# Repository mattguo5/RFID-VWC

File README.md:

# RFID-VWC

The RFID-VWC Github repository serves to document all of the hardware and software implementations for the Oregon State University OPEnS RFID Moisture project.

Directory information:

BOM

    - Contains the most up-to-date BOM of the overall project
  
Code

  - Adafruit_Logging
  
        - Contains the most up-to-date Adafruit STEMMA Soil Moisture firmware code
      
  - Implementation
  
        - Contains the Feather M0 port of firmware for the RFID Sensor
  - src
  
        - Includes all dependencies needed to compile the above .ino files
      
Hardware

    -Contains .brd and .sch files of the RFID-Feather Interface Boards for communication with the Feather M0

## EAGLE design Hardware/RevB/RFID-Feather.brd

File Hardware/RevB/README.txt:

Here contains the board and schematic files for the RevB board Interface Board.

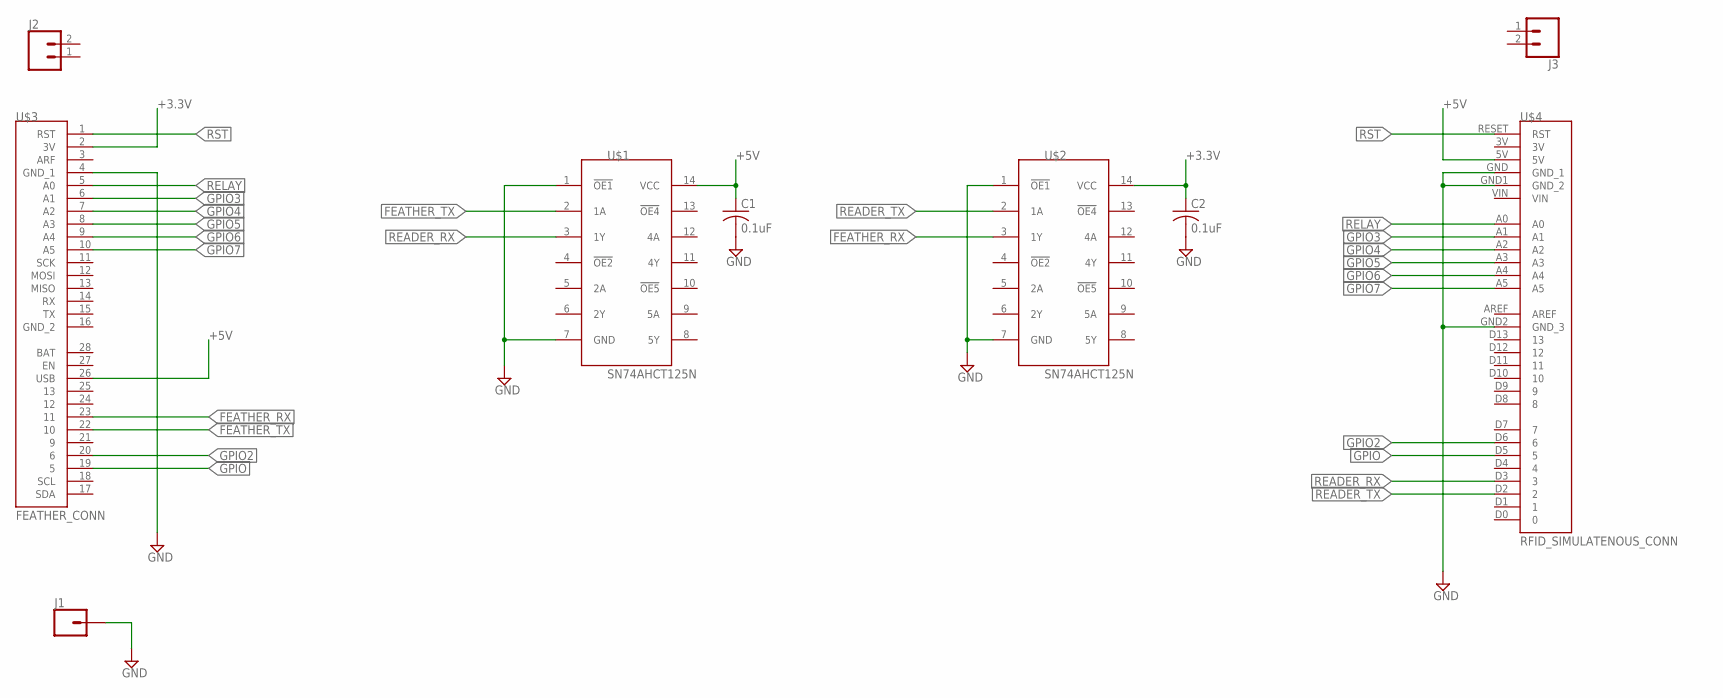
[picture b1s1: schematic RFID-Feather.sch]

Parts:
C1, C2: 0.1uF; C0805K
J1: CONN_01PTH_2MM; 1X01_2MM
J2, J3: CONN_02; 1X02
U$1, U$2: SN74AHCT125N; DIP254P762X508-14P
U$3: FEATHER_CONN; FEATHERWING
U$4: RFID_SIMULATENOUS_CONN; ARDUINO

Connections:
+3.3V: C2.1, U$2.14 (VCC), U$3.2 (3V)
+5V: C1.1, U$1.14 (VCC), U$3.26 (USB), U$4.5V
FEATHER_RX: U$2.3 (1Y), U$3.23 (11)
FEATHER_TX: U$1.2 (1A), U$3.22 (10)
GND: C1.2, C2.2, J1.1, U$1.1 (!OE1), U$1.7 (GND), U$2.1 (!OE1), U$2.7 (GND), U$3.4 (GND_1), U$4.GND (GND_1), U$4.GND1 (GND_2), U$4.GND2 (GND_3)
GPIO: U$3.19 (5), U$4.D5 (5)
GPIO2: U$3.20 (6), U$4.D6 (6)
GPIO3: U$3.6 (A1), U$4.A1
GPIO4: U$3.7 (A2), U$4.A2
GPIO5: U$3.8 (A3), U$4.A3
GPIO6: U$3.9 (A4), U$4.A4
GPIO7: U$3.10 (A5), U$4.A5
READER_RX: U$1.3 (1Y), U$4.D3 (3)
READER_TX: U$2.2 (1A), U$4.D2 (2)
RELAY: U$3.5 (A0), U$4.A0
RST: U$3.1 (RST), U$4.RESET (RST)

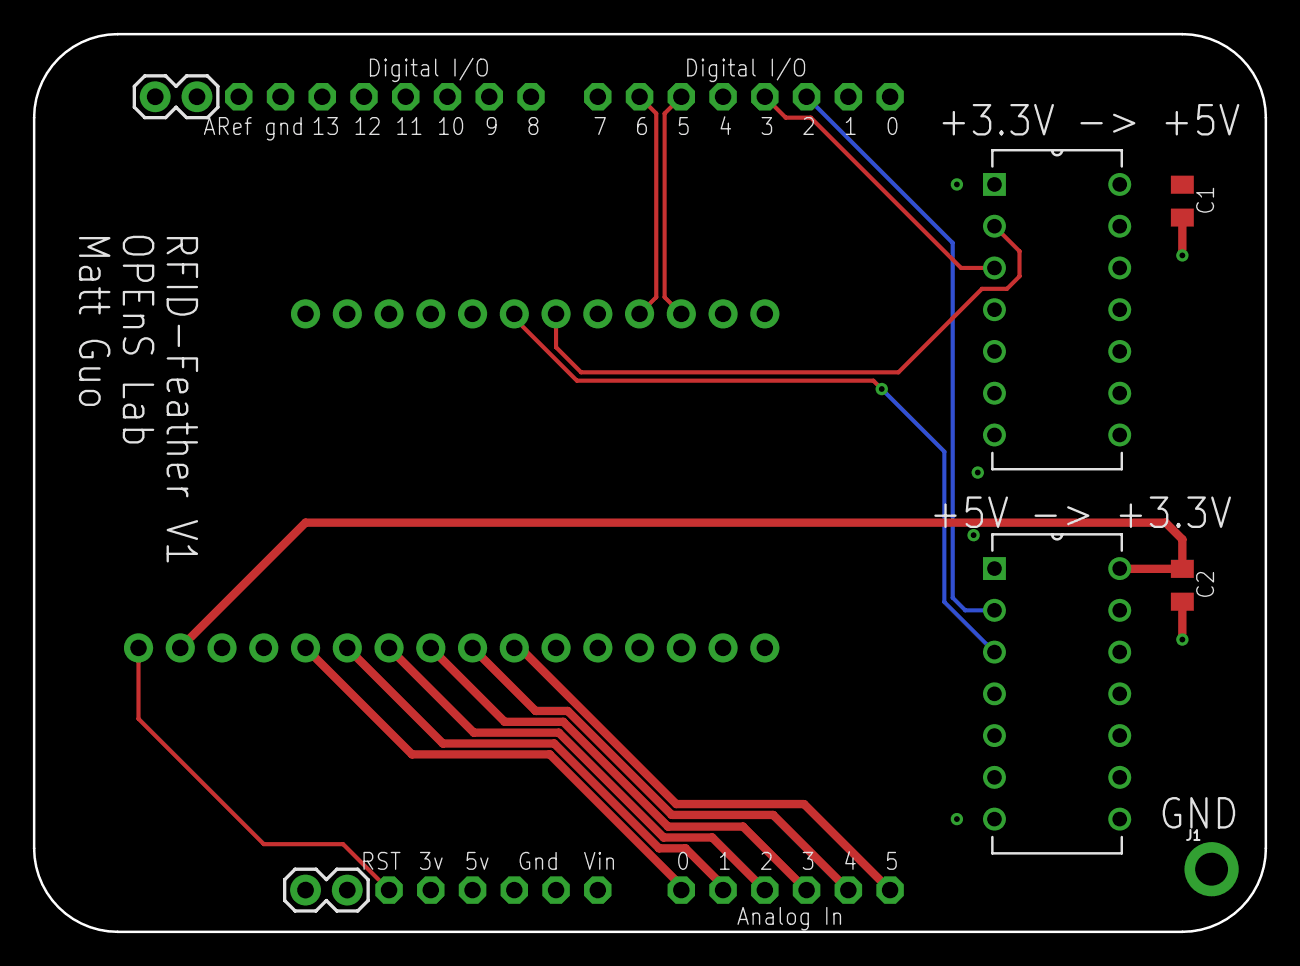
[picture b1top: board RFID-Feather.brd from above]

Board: 2 copper layers, 74.9 x 54.6 mm, 9 parts (0 on the bottom side), 16 nets.

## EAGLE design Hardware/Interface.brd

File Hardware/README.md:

This is the .sch and .brd of the interface board for the Sparkfun RFID reader and Feather M0

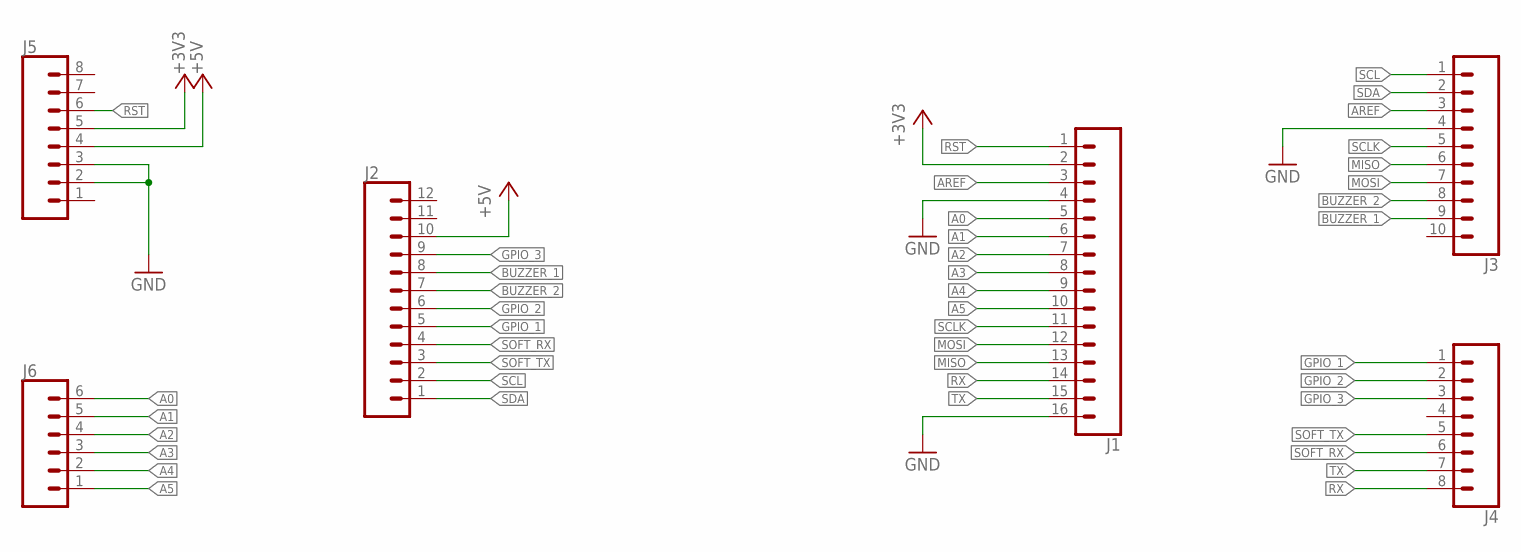
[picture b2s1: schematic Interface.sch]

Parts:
J1: CONN_16; 1X16
J2: CONN_12; 1X12
J3: CONN_10"; 1X10
J4, J5: CONN_08"; 1X08
J6: CONN_06SILK_FEMALE_PTH; 1X06

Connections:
+3V3: J1.2, J5.5
+5V: J2.10, J5.4
A0: J1.5, J6.6
A1: J1.6, J6.5
A2: J1.7, J6.4
A3: J1.8, J6.3
A4: J1.9, J6.2
A5: J1.10, J6.1
AREF: J1.3, J3.3
BUZZER_1: J2.8, J3.9
BUZZER_2: J2.7, J3.8
GND: J1.4, J1.16, J3.4, J5.2, J5.3
GPIO_1: J2.5, J4.1
GPIO_2: J2.6, J4.2
GPIO_3: J2.9, J4.3
MISO: J1.13, J3.6
MOSI: J1.12, J3.7
RST: J1.1, J5.6
RX: J1.14, J4.8
SCL: J2.2, J3.1
SCLK: J1.11, J3.5
SDA: J2.1, J3.2
SOFT_RX: J2.4, J4.6
SOFT_TX: J2.3, J4.5
TX: J1.15, J4.7

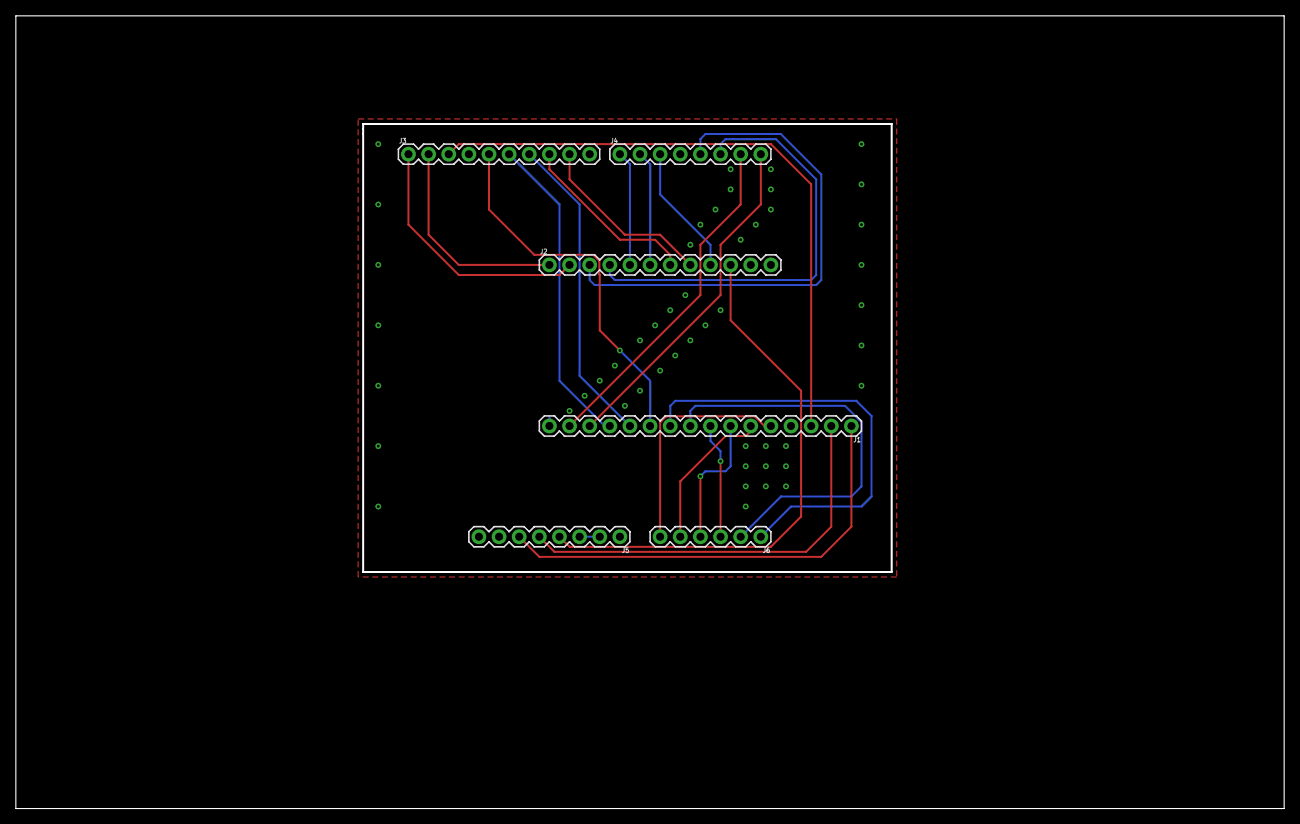
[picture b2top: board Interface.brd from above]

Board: 2 copper layers, 160.0 x 100.0 mm, 6 parts (0 on the bottom side), 25 nets.

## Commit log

2019-04-02 Created src directory
2019-04-23 Updated Library
2019-05-21 Arduino Demo
2020-03-13 Pushed Most Recent Adafruit Soil Sensor Code
2020-03-13 Added Fertigate Functionality
2020-03-13 Added Logger-Box BOM
2020-10-17 Added Feather M0 skeleton code
2020-10-22 Added Feather EPC Write Script

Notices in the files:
parts and their libraries:
SparkFun-Connectors: Licensing: Creative Commons ShareAlike 4.0 International - https://creativecommons.org/licenses/by-sa/4.0
